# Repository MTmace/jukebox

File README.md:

# Jukebox

A 1970s Seeburg USC2 Firestar converted to play digital music. A Raspberry Pi 5 runs
[Fruitbox v3](https://github.com/chundermike/fruitbox-v3) on a 34" ultrawide screen under the
glass. The original keypad and coin slot are kept as inputs, through a Teensy 4.1
(an Arduino-compatible board) that acts as a USB keyboard. Music comes from a Windows share; playlists made on Windows decide which songs are on
the jukebox. Audio goes from an InnoMaker HiFi DAC HAT to a bridged Blaupunkt car amplifier.

**See the [wiki](https://github.com/MTmace/Jukebox/wiki) for photos and a guided tour of the build.**

## What's in each folder

**Runs on the Pi**

| Folder | What it is | Where it goes on the Pi |
|---|---|---|
| `fruitbox/` | Fruitbox settings (`fruitbox.ini`), the launcher, screen and autostart setup | `/home/mtmace/fruitbox/` |
| `skin/` | The "Firestar Ultrawide" skin. `Firestar Ultrawide/` is the skin itself; `build_skin.py` and `status_screen.py` generate it | `Firestar Ultrawide/` goes to `/opt/fruitbox/skins/Firestar Ultrawide/` |
| `library/` | Music library: mount the Windows share, turn the playlists into categories, short strip titles, the nightly update. Start with `SETUP-GUIDE.md` | `/home/mtmace/fruitbox/` |
| `state-manager/` | Service `jukebox-state`: decides if the jukebox is starting, active, idle, in attract mode or asleep; handles the Sleep, Reboot, Rebuild Playlist and Shut Down keys | `/usr/local/bin/` and a systemd service |
| `cabinet-lights/` | Service `jukebox-lights`: the LED strips around the cabinet, driven straight from a Pi pin, following the jukebox's state | `/usr/local/bin/`, settings in `/home/mtmace/fruitbox/` |
| `status-page/` | Service `jukebox-status`: the status and control web page (http://jukebox.local) and the F24 on-screen status box | `/usr/local/bin/` and a systemd service |
| `macro-pad/` | The Koolertron macro pad's key and knob settings, and service `jukebox-bass` (the bass knob) | `/home/mtmace/fruitbox/` and a user service |

**Runs on the Teensy**

| Folder | What it is |
|---|---|
| `arduino/` | Teensy 4.1 program for the Seeburg keypad, coins, buttons and the selection number lights, plus wiring notes and a beginner guide. Uploaded from the Arduino IDE |

**Everything else**

| Folder | What it is |
|---|---|
| `3dPrints/` | Every 3D-printed part: keycaps, Pi and Teensy cases, lamp panel, button bar, splice holders, WAGO boxes, power inlet plate, status screen frame and more. Each folder has a README |
| `docs/` | Build notes: monitor mounting and volume |
| `PARTS.md` | Every part for the build and whether it is bought yet |

## Notes

- Run scripts with `bash` or `python3` in front, e.g.
  `bash /home/mtmace/fruitbox/update-jukebox.sh`. Files downloaded or copied from Windows lose
  their "executable" setting. After copying `.sh` files to the Pi, run
  `chmod +x /home/mtmace/fruitbox/*.sh` once so the nightly job can start them.
- The skin folder name has a space in it, so put quotes around its path in commands:
  `sudo cp -r "/home/mtmace/Firestar Ultrawide" /opt/fruitbox/skins/`
- `.gitattributes` keeps Linux line endings on the scripts, so they still run after a trip
  through Windows.
- The skin's fonts and sounds come from Fruitbox's own stock skins. To rebuild the skin, run
  `FRUITBOX_SKINS=/opt/fruitbox/skins python3 build_skin.py` from `Fruitbox/Skins` on the Pi.

## License

MIT, see [LICENSE](LICENSE). The Seeburg name and logo, Fruitbox's fonts and sounds, and the
Bootstrap Icons keep their own owners' terms.

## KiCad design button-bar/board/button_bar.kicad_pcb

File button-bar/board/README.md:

# Glass button bar, no-solder board version

Same four buttons as the ribbon version one folder up (page left, page right,
genre, random song), but the switches push into sockets on a small circuit board and
the cable plugs in. If the board is ordered **with assembly**, the factory solders
the sockets and the plug, and you do no soldering at all.

- Board: 98.75 x 21 mm.
- Case: a low, sloped shape with rounded top edges and two sunken keycap wells,
  so it looks like part of the trim rather than a box. About 116 x 38 mm
  (4½" x 1½") where it meets the glass, 104 x 26 mm across the top, and 13 mm
  (½") tall. Keycaps stand about 2 mm above the top. No screw heads show: the
  screws go in from underneath.
- The plug points out of the right-hand end of the bar.

## Files

| File | What it is |
|---|---|
| `button_bar_gerbers.zip` | Upload this to the board maker (JLCPCB, PCBWay, etc.). |
| `jlc_bom.csv`, `jlc_cpl.csv` | Parts list and parts positions for JLCPCB's assembly option. |
| `button_bar_case_tray.stl`, `button_bar_case_lid.stl` | 3D-print files for the case. |
| `button_bar_pcb_case.scad` | Editable case (OpenSCAD, free). |
| `button_bar.kicad_pcb`, `make_pcb.py` | Board design (KiCad 7). `make_pcb.py` rebuilds it. |

## Ordering the board (JLCPCB)

1. Go to jlcpcb.com, click **Order now**, and upload `button_bar_gerbers.zip`.
   Leave the defaults (2 layers, 1.6 mm). Pick a black solder mask if you like.
2. Turn on **PCB Assembly**. Choose **assemble bottom side** for the sockets, and
   also the top side (through-hole) for the plug. Quantity 2 is enough.
3. Upload `jlc_bom.csv` and `jlc_cpl.csv` when asked. The sockets are LCSC part
   **C5333465** (Kailh CPG135001S30). The plug is **JST S6B-PH-K-S**; if their
   search does not match it, type that name into the part search.
4. On the placement preview, check each socket's two square pads line up with
   the socket drawing. Rotate it there if not.

If you'd rather save money and solder 14 easy joints yourself, skip assembly and buy
the sockets and plug separately (search "Kailh Choc hotswap socket" and
"JST PH 6 pin right angle").

## Other parts

| Qty | Part | Notes |
|---|---|---|
| 4 | Kailh Choc **v1** switches | White = clicky, Brown = tactile bump. |
| 4 | Choc v1 keycaps | Blank caps plus a small decal work fine. |
| 1 | **JST PH 2.0 mm, 6-pin to Dupont female** cable | The Dupont end pushes onto Pro Micro header pins. Measure the run from the bar to the Pro Micro; if it is longer than the cables on sale, add a JST PH 6-pin extension. |
| 4 | M2 x 10 mm **countersunk (flat-head)** self-tapping screws | Go in from underneath, through the tray and board, into the lid. |
| 1 | 3M VHB tape, clear (4910) | Sticks the bar to the glass. |

## Wiring (cable plug to Pro Micro)

| Plug pin | Signal | Pro Micro pin | Fruitbox action |
|---|---|---|---|
| 1 | Ground | GND | |
| 2 | ◀ | 15 | Page left (Left arrow) |
| 3 | ▶ | A1 | Page right (Right arrow) |
| 4 | Genre | 7 | Genre (Right Alt) |
| 5 | Random song | A3 | Adds one random song to the queue (Space) |
| 6 | spare | | |

Pin 1 is marked with a square pad on the board and on the back silkscreen.
Cable colours vary by seller, so follow the pin numbers, not the colours.

## Assembly

1. Print the tray (bottom down) and lid (the STL is already flipped, top down).
   Black PETG or matte black PLA. 0.2 mm layers are fine.
2. Lay the board in the tray, sockets facing down, plug toward the open end.
3. Push the four switches into the board from the top until they seat.
4. Put the lid on. Turn the bar over and drive the four M2 screws in from
   underneath until the heads sit flush. Don't over-tighten: they cut their own
   thread in the plastic.
5. Push the keycaps on. Plug the cable in through the tunnel in the end.
6. Clean the glass with rubbing alcohol, stick the bar down with VHB tape, press
   hard for 30 seconds.

## Not yet checked

- Nothing has been made yet. The socket and switch hole positions follow the
  widely used open-source Choc v1 hot-swap footprint, and the board passes KiCad's
  design check, but check the JLCPCB placement preview before paying.
- Choc heights are from memory: print the lid first and test one switch and cap in
  a well. If the cap rubs or sits too low, change `lid_above` in the .scad file.
- Bar position, depth and cable route wait on the border width and whether the
  glass lid lifts.

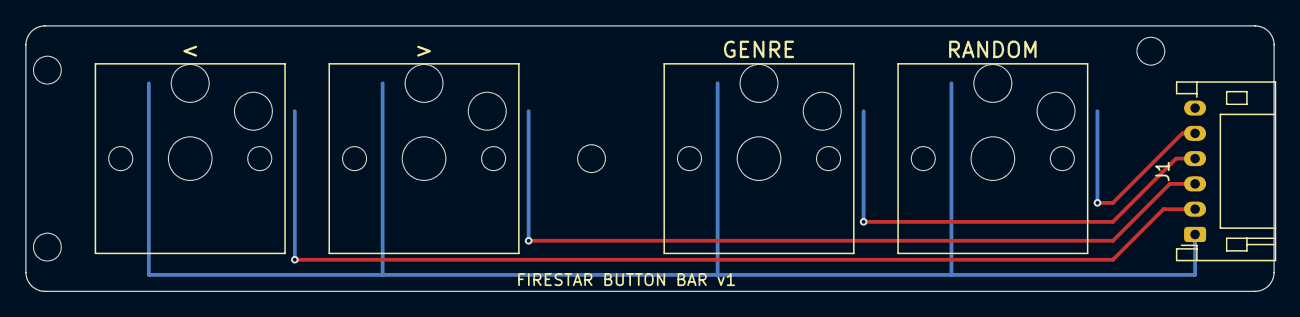
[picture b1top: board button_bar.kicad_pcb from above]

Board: 2 copper layers, 98.8 x 21.0 mm, 9 parts (0 on the bottom side), 5 nets.

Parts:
H1, H2, H3, H4: (no value)
J1: JST_PH_S6B-PH-K_1x06_P2.00mm_Horizontal
SW1, SW2, SW3, SW4: Choc_v1_hotswap

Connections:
GENRE: J1.4, SW3.2
GND: J1.1, SW1.1, SW2.1, SW3.1, SW4.1
LEFT: J1.2, SW1.2
RANDOM: J1.5, SW4.2
RIGHT: J1.3, SW2.2
